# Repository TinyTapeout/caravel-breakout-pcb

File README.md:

# caravel-breakout-pcb - deprecated

> [!WARNING]
> This repo is deprecated. Use [TinyTapeout/breakout-pcb](https://github.com/tinytapeout/breakout-pcb) instead.

A set of breakouts/carrier boards for the Caravel ASIC used in eFabless MPW runs and a little FPGA adapter for simulating the TinyTapeout design, to be used alongside the [Tiny Tapeout 4+ Demo Board](https://github.com/TinyTapeout/tt-demo-pcb), the [Tiny Tapeout 1-3 Demo Board](https://github.com/TinyTapeout/tt123-demo-pcb), and/or other custom designs.

The ASIC board designs are based on the original breakout [published here](https://github.com/efabless/caravel_board/tree/main/hardware/breakout), optimised for single-sided surface mount assembly and ease of integration into other projects.

Design files are in KiCad 6 format, custom library parts can be found in [this external repo](https://github.com/omerk/ok-kicad-libs).

# PCBs sponsored by Aisler!

Thanks [Aisler](https://aisler.net/) for sponsoring our PCB development.

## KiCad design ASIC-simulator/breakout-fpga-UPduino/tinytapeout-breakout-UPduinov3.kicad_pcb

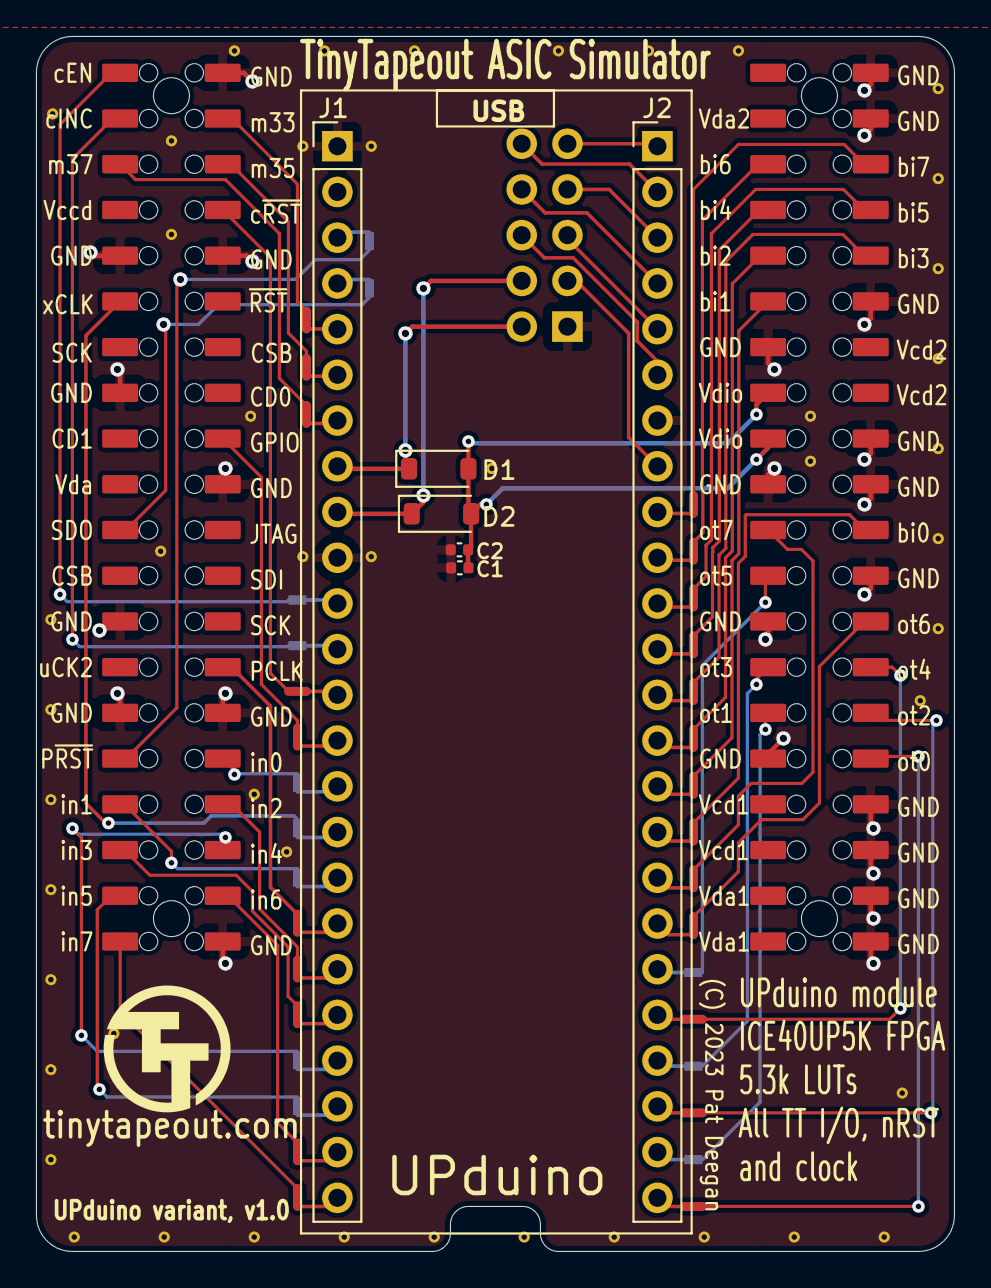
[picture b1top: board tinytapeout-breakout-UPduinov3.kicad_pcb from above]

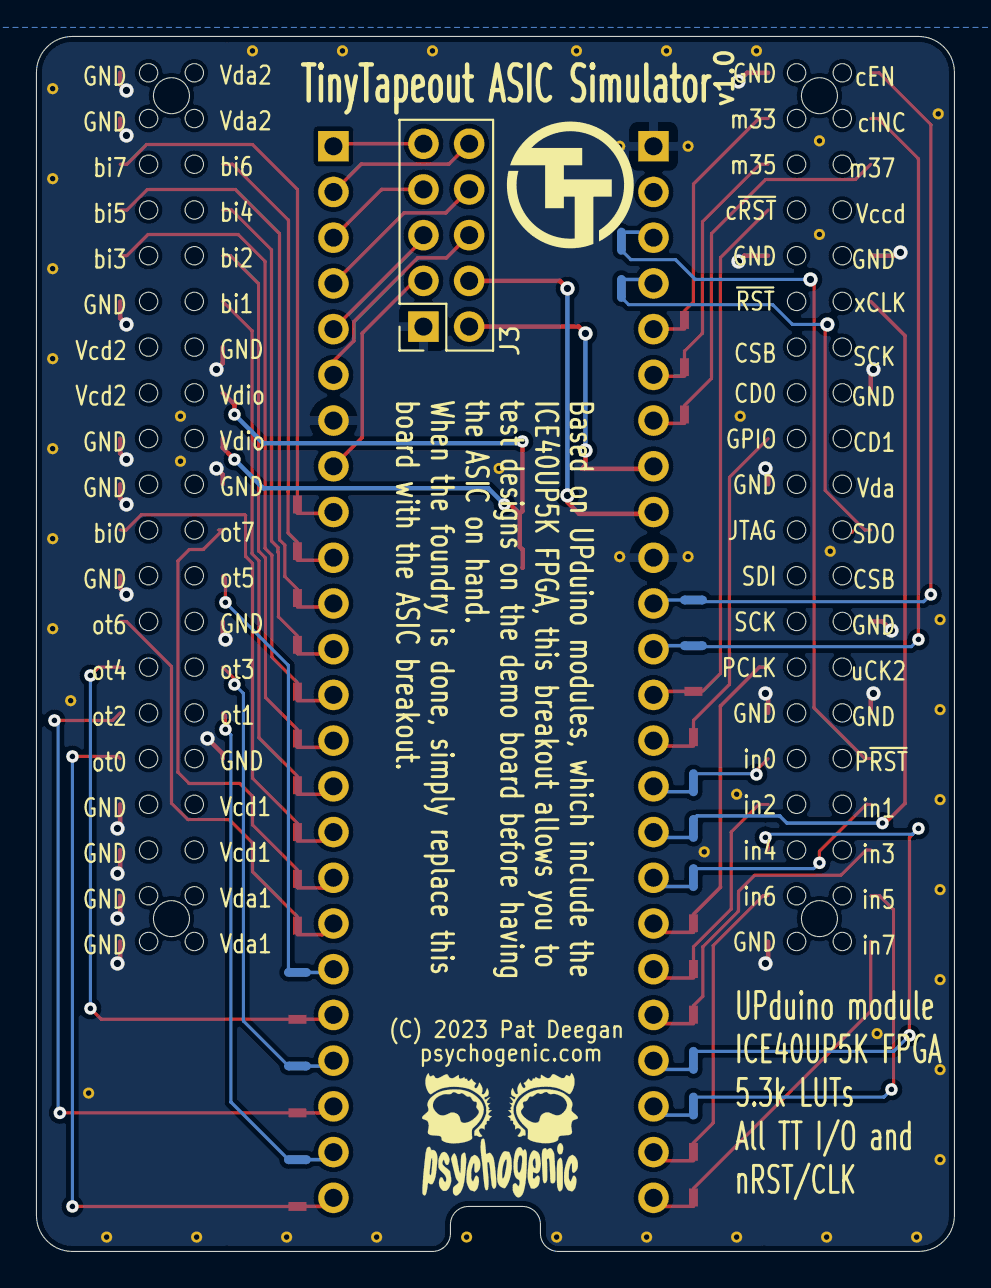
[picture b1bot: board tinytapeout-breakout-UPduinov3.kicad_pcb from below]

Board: 2 copper layers, 51.0 x 67.5 mm, 91 parts (13 on the bottom side), 85 nets.

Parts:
C1, C2: 0.1uf; C_0402_1005Metric
CON1, CON2: REF-182665-01; FH-00339
D1, D2: B0520LW-7-F; D_SOD-123
J1: UPduinoA; PinHeader_1x24_P2.54mm_Vertical
J2: UPduinoB; PinHeader_1x24_P2.54mm_Vertical
J3: Conn_02x05_Odd_Even; PinSocket_2x05_P2.54mm_Vertical
NT1, NT2, NT3, NT4, NT5, NT6, NT7, NT8, NT9, NT10, NT11, NT12, NT13, NT14, NT15, NT16, NT17, NT18, NT19, NT20, NT21, NT22, NT23, NT24, NT25, NT26, NT27, NT28, NT29, NT30, NT31, NT32, NT33, NT34, NT35: NetTie_2; NetTie-2_SMD_Pad0.5mm
STITCH1, STITCH2, STITCH3, STITCH4, STITCH5, STITCH6, STITCH7, STITCH8, STITCH9, STITCH10, STITCH10#2, STITCH10#3, STITCH11, STITCH12, STITCH13, STITCH14, STITCH15, STITCH16, STITCH17, STITCH18, STITCH19, STITCH20, STITCH21, STITCH22, STITCH22#2, STITCH22#3, STITCH22#4, STITCH22#5, STITCH22#6, STITCH22#7, STITCH22#8, STITCH22#9, STITCH22#10, STITCH22#11, STITCH22#12, STITCH22#13, STITCH22#14, STITCH23, STITCH24, STITCH25, STITCH26, STITCH27, STITCH28, STITCH28#2, STITCH28#3, STITCH28#4, STITCH28#5: StitchingVia-0.3mm

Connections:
/3v3UP: D2.1 (K), J1.9, J3.4
/5VUSB: D1.1 (K), J1.8, J3.2
/CDONE: J1.4, NT2.2
/CLK_12M_EXT: J2.8, J3.3
/CRESET_N: J1.3, NT1.2
/FLASH_MISO: J2.4, J3.8
/FLASH_MOSI: J2.3, J3.7
/FT_SCK: J2.2, J3.10
/FT_SSn: J2.1, J3.9
/IOB_0A: J2.23, NT34.2
/IOB_2A: J2.22, NT33.2
/IOB_3B_G6: J2.17, NT28.2
/IOB_4A: J2.20, NT31.2
/IOB_5B: J2.21, NT32.2
/IOB_6A: J2.24, NT35.2
/IOB_8A: J2.18, NT29.2
/IOB_9B: J2.19, NT30.2
/IOB_13B: J2.16, NT27.2
/IOB_16A: J2.15, NT26.2
/IOB_18A: J2.6, J3.6
/IOB_20A: J2.14, NT25.2
/IOB_22A: J2.9, NT20.2
/IOB_23B: J2.10, NT21.2
/IOB_24A: J2.11, NT22.2
/IOB_25B_G3: J2.5, J3.5
/IOB_29B: J2.12, NT23.2
/IOB_31B: J2.13, NT24.2
/IOT_36B: J1.12, NT7.2
/IOT_37A: J1.11, NT6.2
/IOT_38B: J1.14, NT9.2
/IOT_39A: J1.13, NT8.2
/IOT_41A: J1.24, NT19.2
/IOT_42B: J1.17, NT12.2
/IOT_43A: J1.15, NT10.2
/IOT_44B: J1.19, NT14.2
/IOT_45A_G1: J1.18, NT13.2
/IOT_46B_G0: J1.16, NT11.2
/IOT_48B: J1.21, NT16.2
/IOT_49A: J1.20, NT15.2
/IOT_50B: J1.23, NT18.2
/IOT_51A: J1.22, NT17.2
/LED_B: J1.7, NT5.2
/LED_G: J1.6, NT4.2
/LED_R: J1.5, NT3.2
GND: C1.1, C2.1, CON1.2, CON1.9, CON1.10, CON1.15, CON1.20, CON1.25, CON1.29, CON1.30, CON1.40, CON2.2, CON2.4, CON2.12, CON2.13, CON2.18, CON2.19, CON2.20, CON2.24, CON2.25, CON2.31, CON2.34, CON2.36, CON2.38, CON2.40, J1.1, J1.10, J2.7, J3.1, STITCH1.1, STITCH2.1, STITCH3.1, STITCH4.1, STITCH5.1, STITCH6.1, STITCH7.1, STITCH8.1, STITCH9.1, STITCH10.1, STITCH10#2.1, STITCH10#3.1, STITCH11.1, STITCH12.1, STITCH13.1, STITCH14.1, STITCH15.1, STITCH16.1, STITCH17.1, STITCH18.1, STITCH19.1, STITCH20.1, STITCH21.1, STITCH22.1, STITCH22#2.1, STITCH22#3.1, STITCH22#4.1, STITCH22#5.1, STITCH22#6.1, STITCH22#7.1, STITCH22#8.1, STITCH22#9.1, STITCH22#10.1, STITCH22#11.1, STITCH22#12.1, STITCH22#13.1, STITCH22#14.1, STITCH23.1, STITCH24.1, STITCH25.1, STITCH26.1, STITCH27.1, STITCH28.1, STITCH28#2.1, STITCH28#3.1, STITCH28#4.1, STITCH28#5.1
SDO/mio[1]: CON1.21, NT2.1
clk/mio[6]: CON1.28, NT13.1
ctrl_ena/mio[32]: CON1.1, NT6.1
ctrl_sel_inc/mio[34]: CON1.3, NT7.1
gpio: CON1.18, NT9.1
mio[33]: CON1.4, NT3.1
mio[35]: CON1.6, NT4.1
mio[37]: CON1.5, NT5.1
ui_in[0]/mio[8]: CON1.32, NT10.1
ui_in[1]/mio[9]: CON1.33, NT12.1
ui_in[2]/mio[10]: CON1.34, NT14.1
ui_in[3]/mio[11]: CON1.35, NT15.1
ui_in[4]/mio[12]: CON1.36, NT16.1
ui_in[5]/mio[13]: CON1.37, NT17.1
ui_in[6]/mio[14]: CON1.38, NT18.1
ui_in[7]/mio[15]: CON1.39, NT19.1
uio[0]/mio[24]: CON2.22, NT27.1
uio[1]/mio[25]: CON2.11, NT26.1
uio[2]/mio[26]: CON2.9, NT25.1
uio[3]/mio[27]: CON2.10, NT24.1
uio[4]/mio[28]: CON2.7, NT23.1
uio[5]/mio[29]: CON2.8, NT22.1
uio[6]/mio[30]: CON2.5, NT21.1
uio[7]/mio[31]: CON2.6, NT20.1
uo_out[0]/mio[16]: CON2.32, NT35.1
uo_out[1]/mio[17]: CON2.29, NT34.1
uo_out[2]/mio[18]: CON2.30, NT33.1
uo_out[3]/mio[19]: CON2.27, NT32.1
uo_out[4]/mio[20]: CON2.28, NT31.1
uo_out[5]/mio[21]: CON2.23, NT30.1
uo_out[6]/mio[22]: CON2.26, NT29.1
uo_out[7]/mio[23]: CON2.21, NT28.1
vccd1: CON2.33, CON2.35
vccd2: CON2.14, CON2.16
vdda1: CON2.37, CON2.39
vdda2: CON2.1, CON2.3
vddio: C1.2, C2.2, CON2.15, CON2.17, D1.2 (A), D2.2 (A)
xclk: CON1.11, NT11.1
~ctrl_sel_rst/mio[36]: CON1.8, NT8.1
~rst/mio[7]: CON1.31, NT1.1

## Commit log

2022-06-16 cleanup unused symbols
2022-12-21 rename boards/re-org repo
2022-12-21 update ignores
2022-12-21 add caravel qfn and bitsy libs
2022-12-24 remove libs
    moved to https://github.com/omerk/ok-kicad-libs
2022-12-24 WIP checkin for comments
2023-02-05 initial check-in for RevA1
2023-06-20 Update to logos, resource refactor, kicad 7 migration
2023-06-20 Revision A2 release and re-org
2023-06-20 basic documentation
2023-06-20 Added fids and patch over-reliance on gnd fill for conn DRC fails
2023-06-21 doc update
2023-07-17 kicad 7 migration, qfn symbol and wiring
2023-07-17 use git for versionning
2023-07-17 RevA1 removed from paths
2023-07-17 pre-route, DRC setup, floorplan for 2-layer top
2023-07-17 routing prelim complete
2023-07-17 sheet and origin cleanup
2023-07-17 v2.0
2023-07-21 QFN breakout v2.1: fixes to footprint s.masks, cleanup, flipped logos
2023-07-26 footprint for cheaper chinese header
2023-07-26 aisler requested mods
2023-07-26 QFN v2.2, using cheaper FH-00339 headers
2023-10-20 docs: update broken links
2023-11-22 QFN breakout sanity naming for nets
2023-11-22 v3.0, breaking changes for ultra-goodness: EMC,TT pinout, FPGA
2023-11-22 Comments and cleanup
2023-11-22 aisler bridge markers
2023-11-23 Added deglitch/delay on Caravel nRST
2023-11-23 Silkscreen cleanup
2023-11-29 Initial ASIC FPGA simulator breakouts import
2023-12-06 FPGA breakout, TT3 ICE40UP5K, initial commit
2023-12-18 ICE40UP5K TT3 breakout, BOM tweaks pre-PCBA first run
2024-01-10 PCBA mods, new boot selector switch
2024-01-12 v1.2 ready for pcba
2024-01-12 documentation
2024-01-12 PCBA BOM and placement CSVs
2024-01-12 gerber reorg
2024-03-22 TT03p5, as fabbed
2024-03-22 v3.2 moved to bottom side pin headers
2024-06-10 docs: add deprecation notice to README

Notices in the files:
ASIC-simulator/breakout-fpga-UPduino/tinytapeout-breakout-UPduinov3.kicad_pcb:
(C) 2023 Pat Deegan
